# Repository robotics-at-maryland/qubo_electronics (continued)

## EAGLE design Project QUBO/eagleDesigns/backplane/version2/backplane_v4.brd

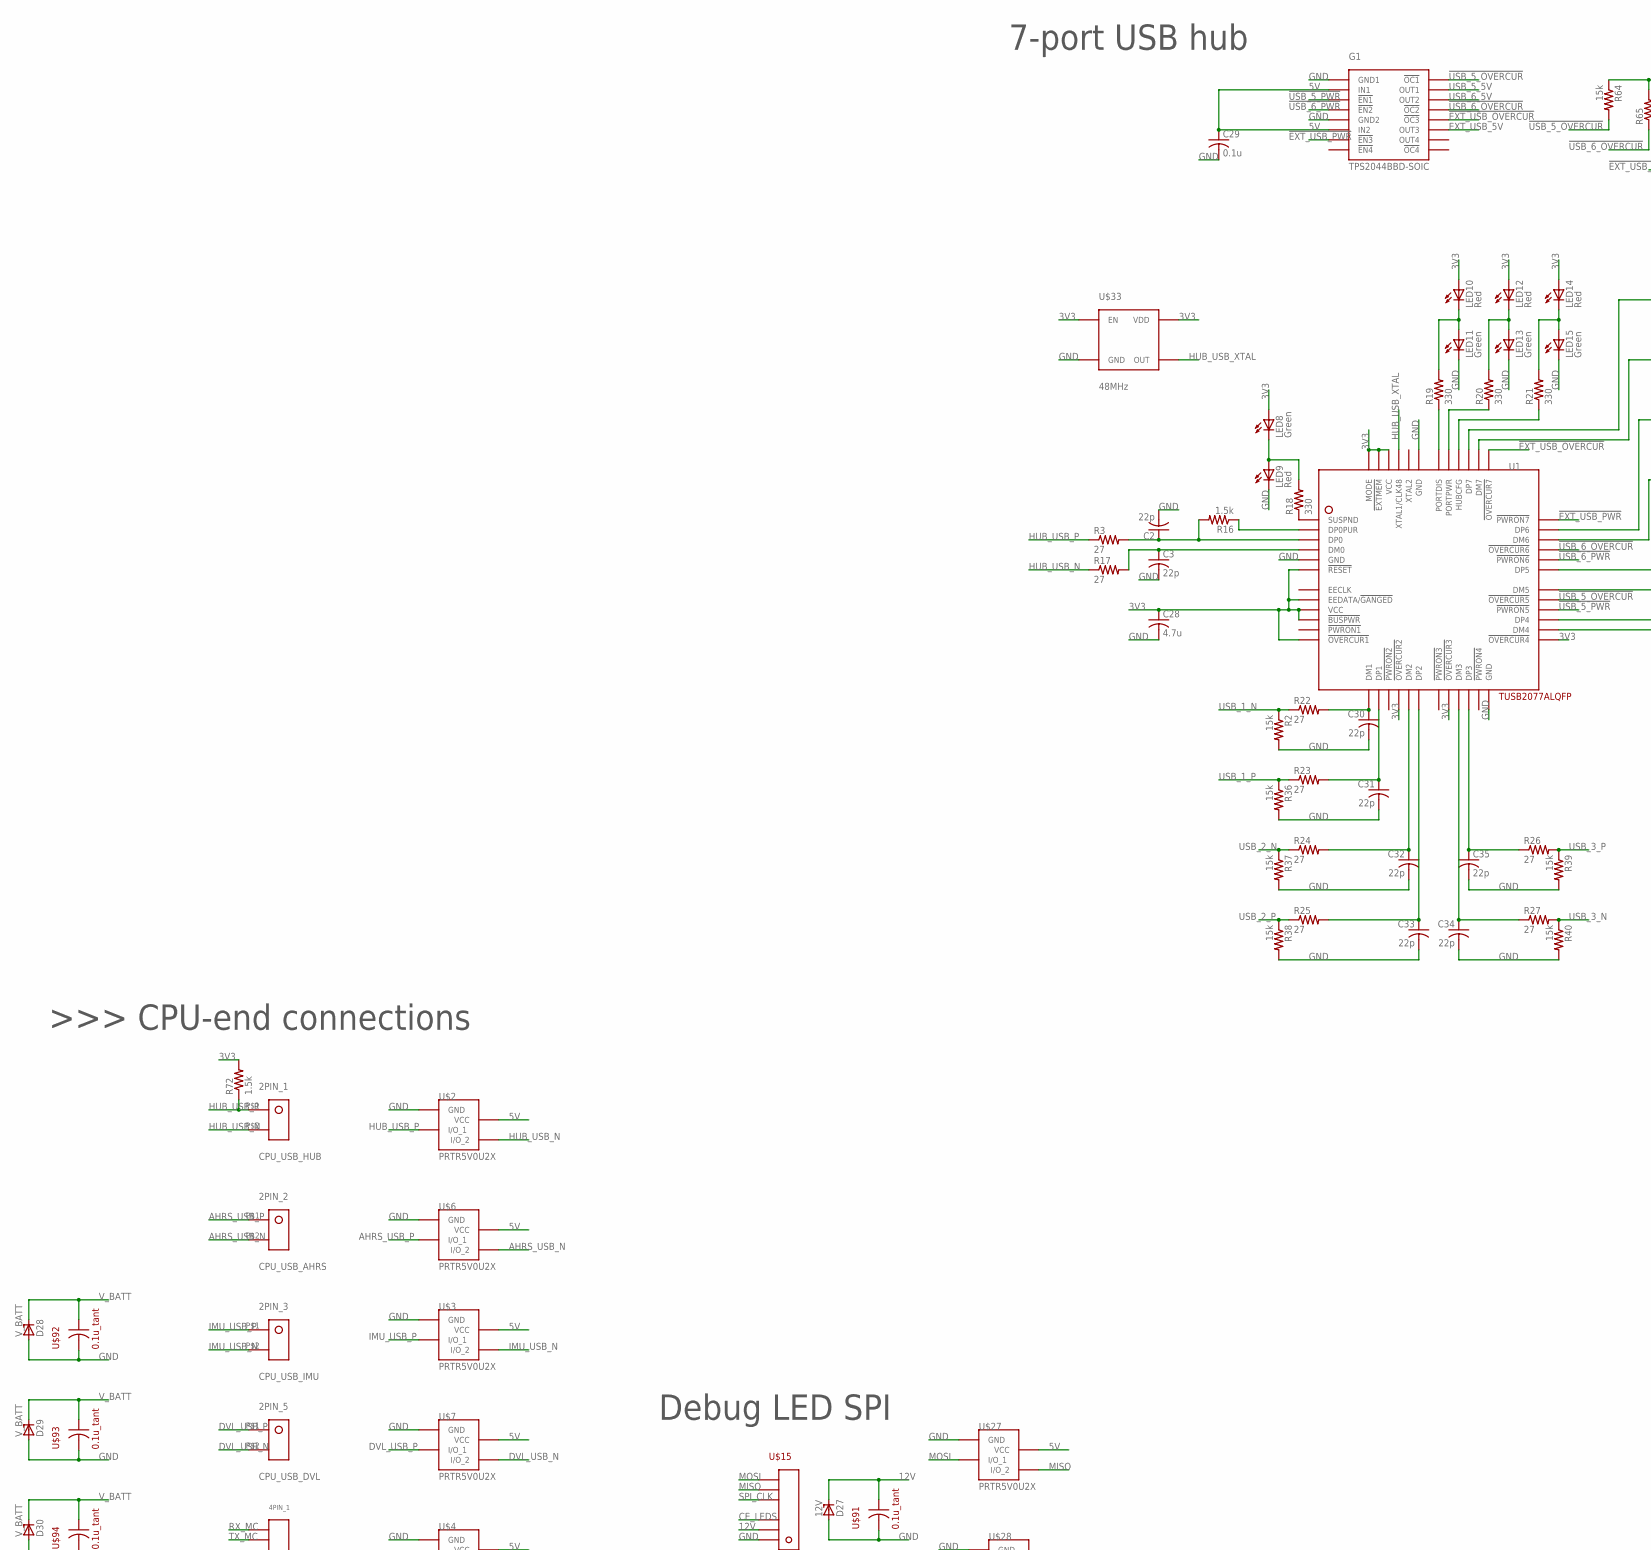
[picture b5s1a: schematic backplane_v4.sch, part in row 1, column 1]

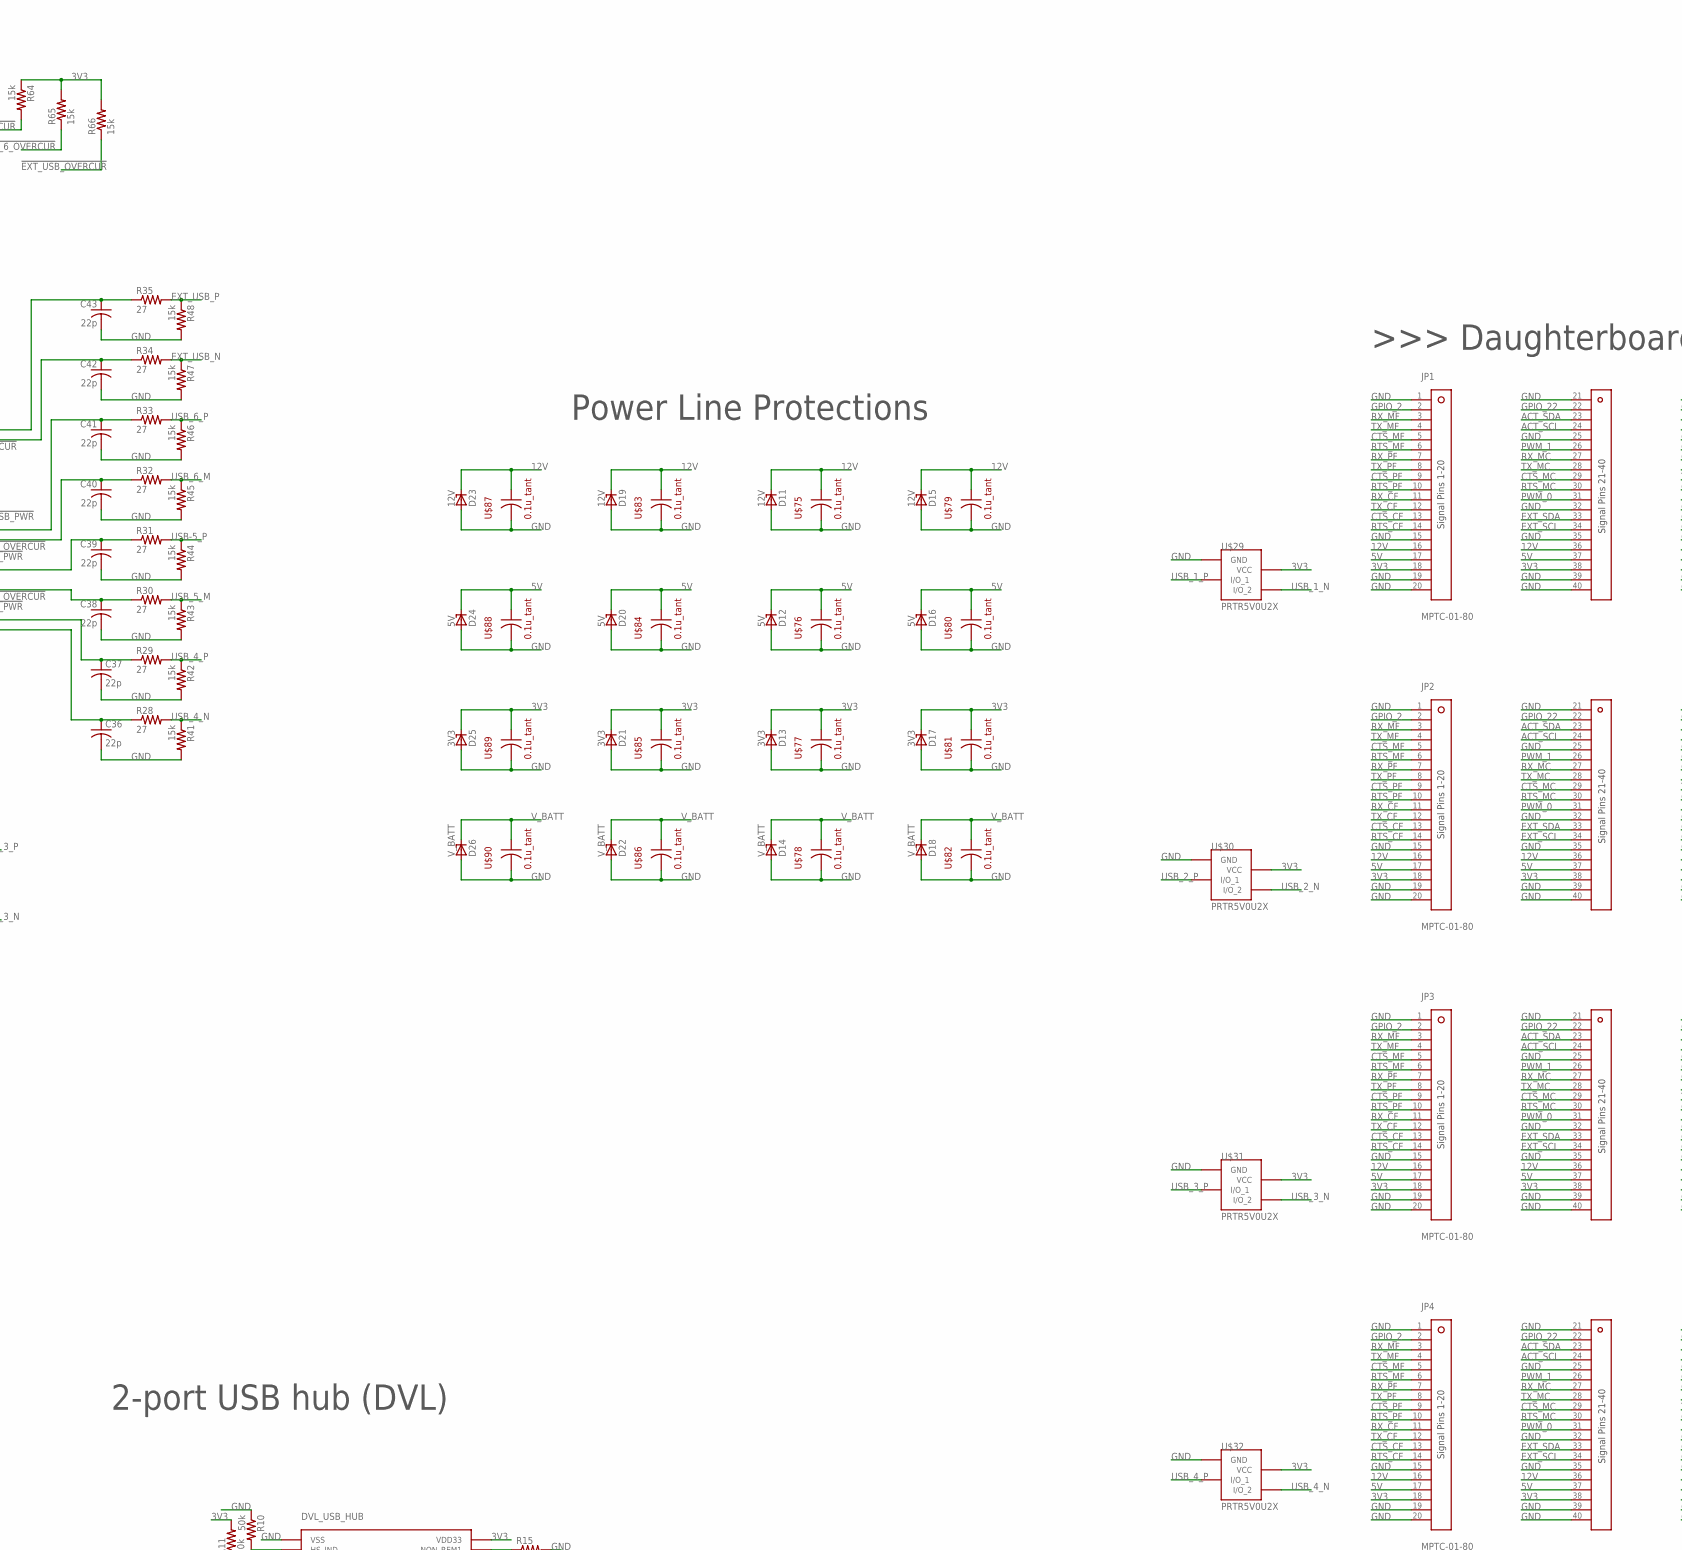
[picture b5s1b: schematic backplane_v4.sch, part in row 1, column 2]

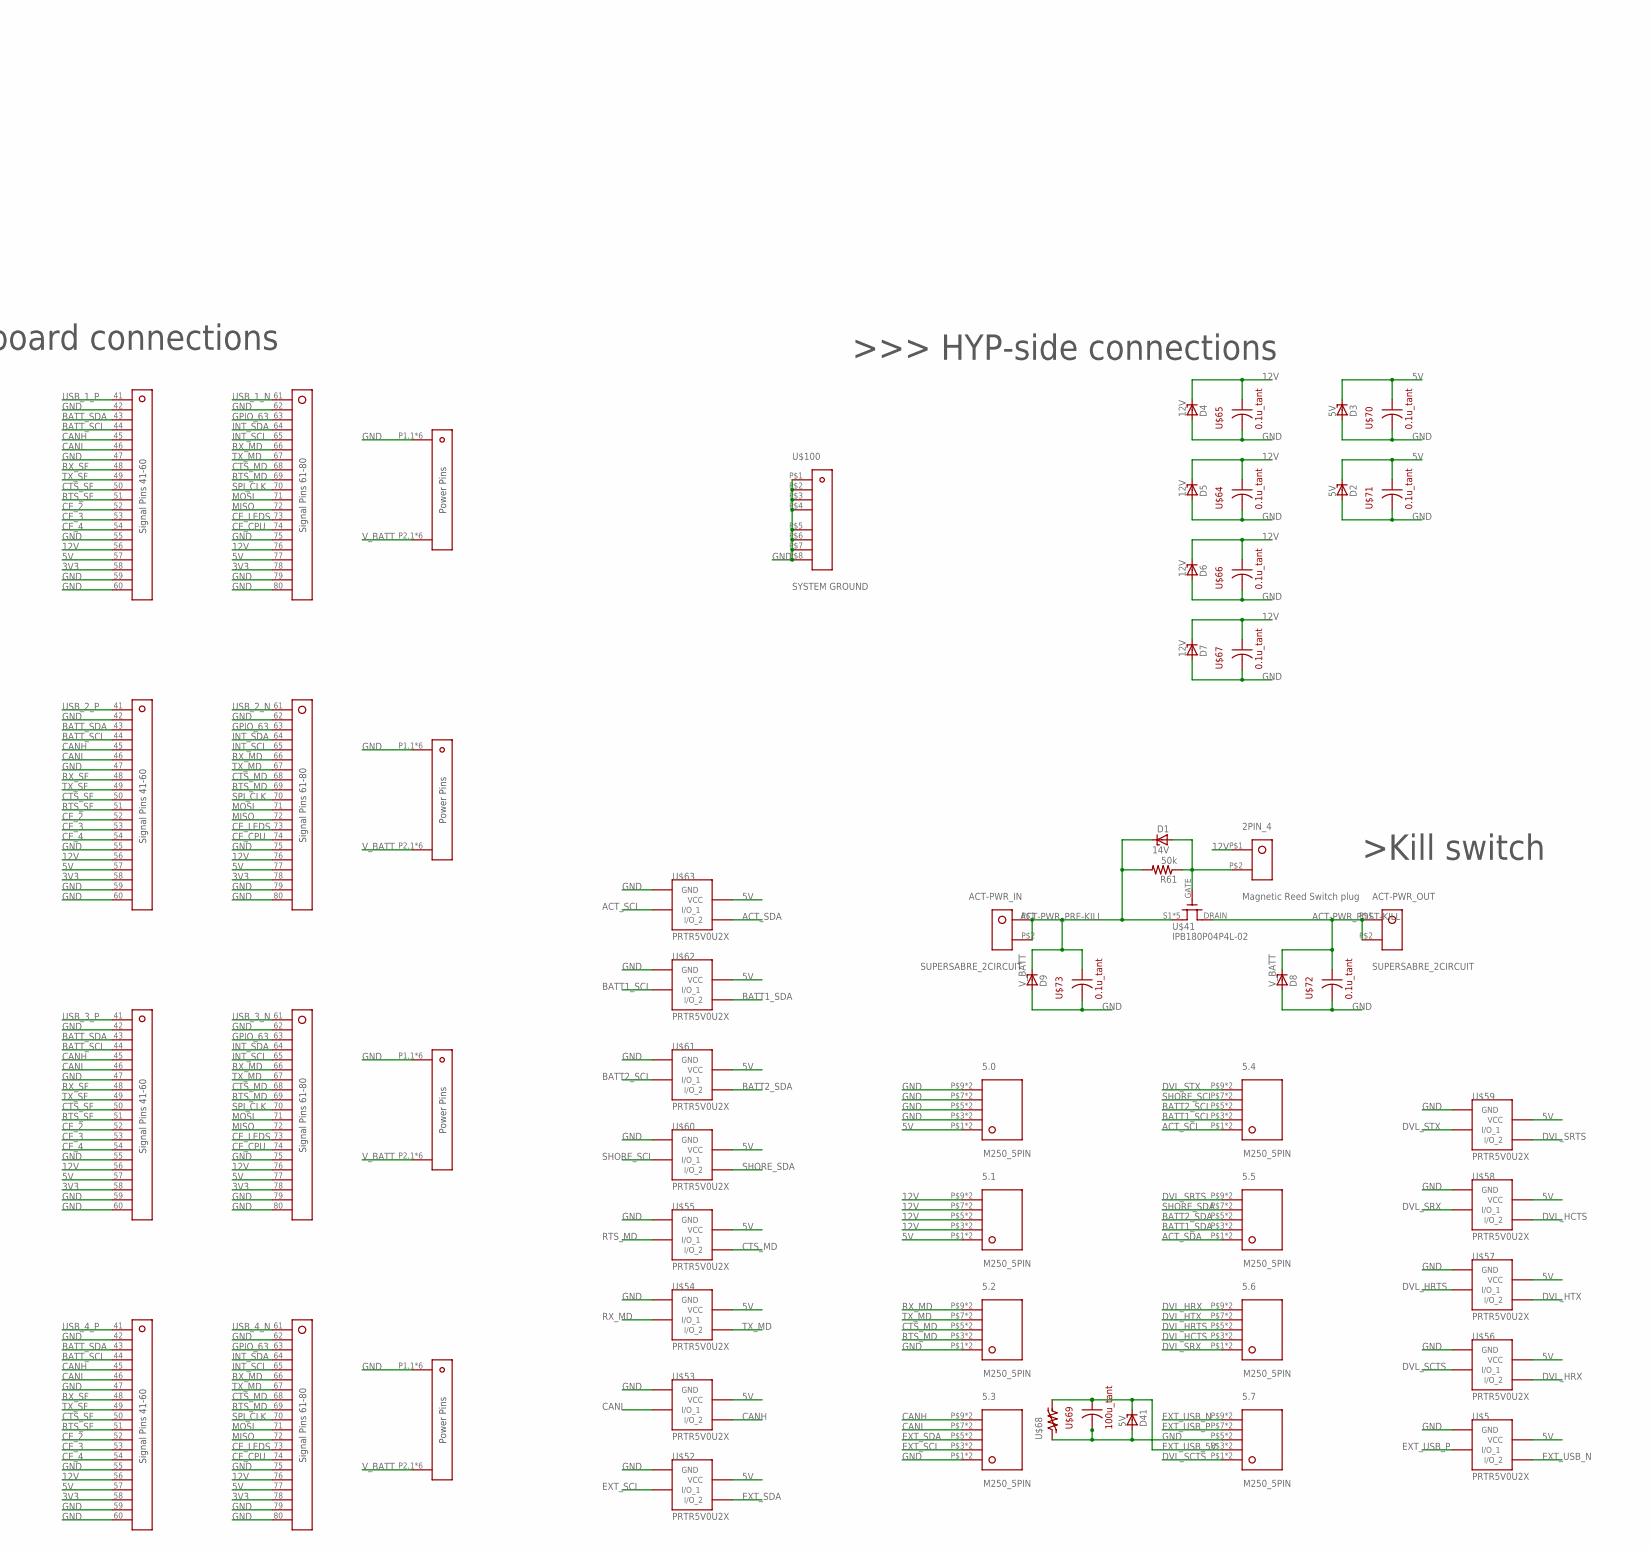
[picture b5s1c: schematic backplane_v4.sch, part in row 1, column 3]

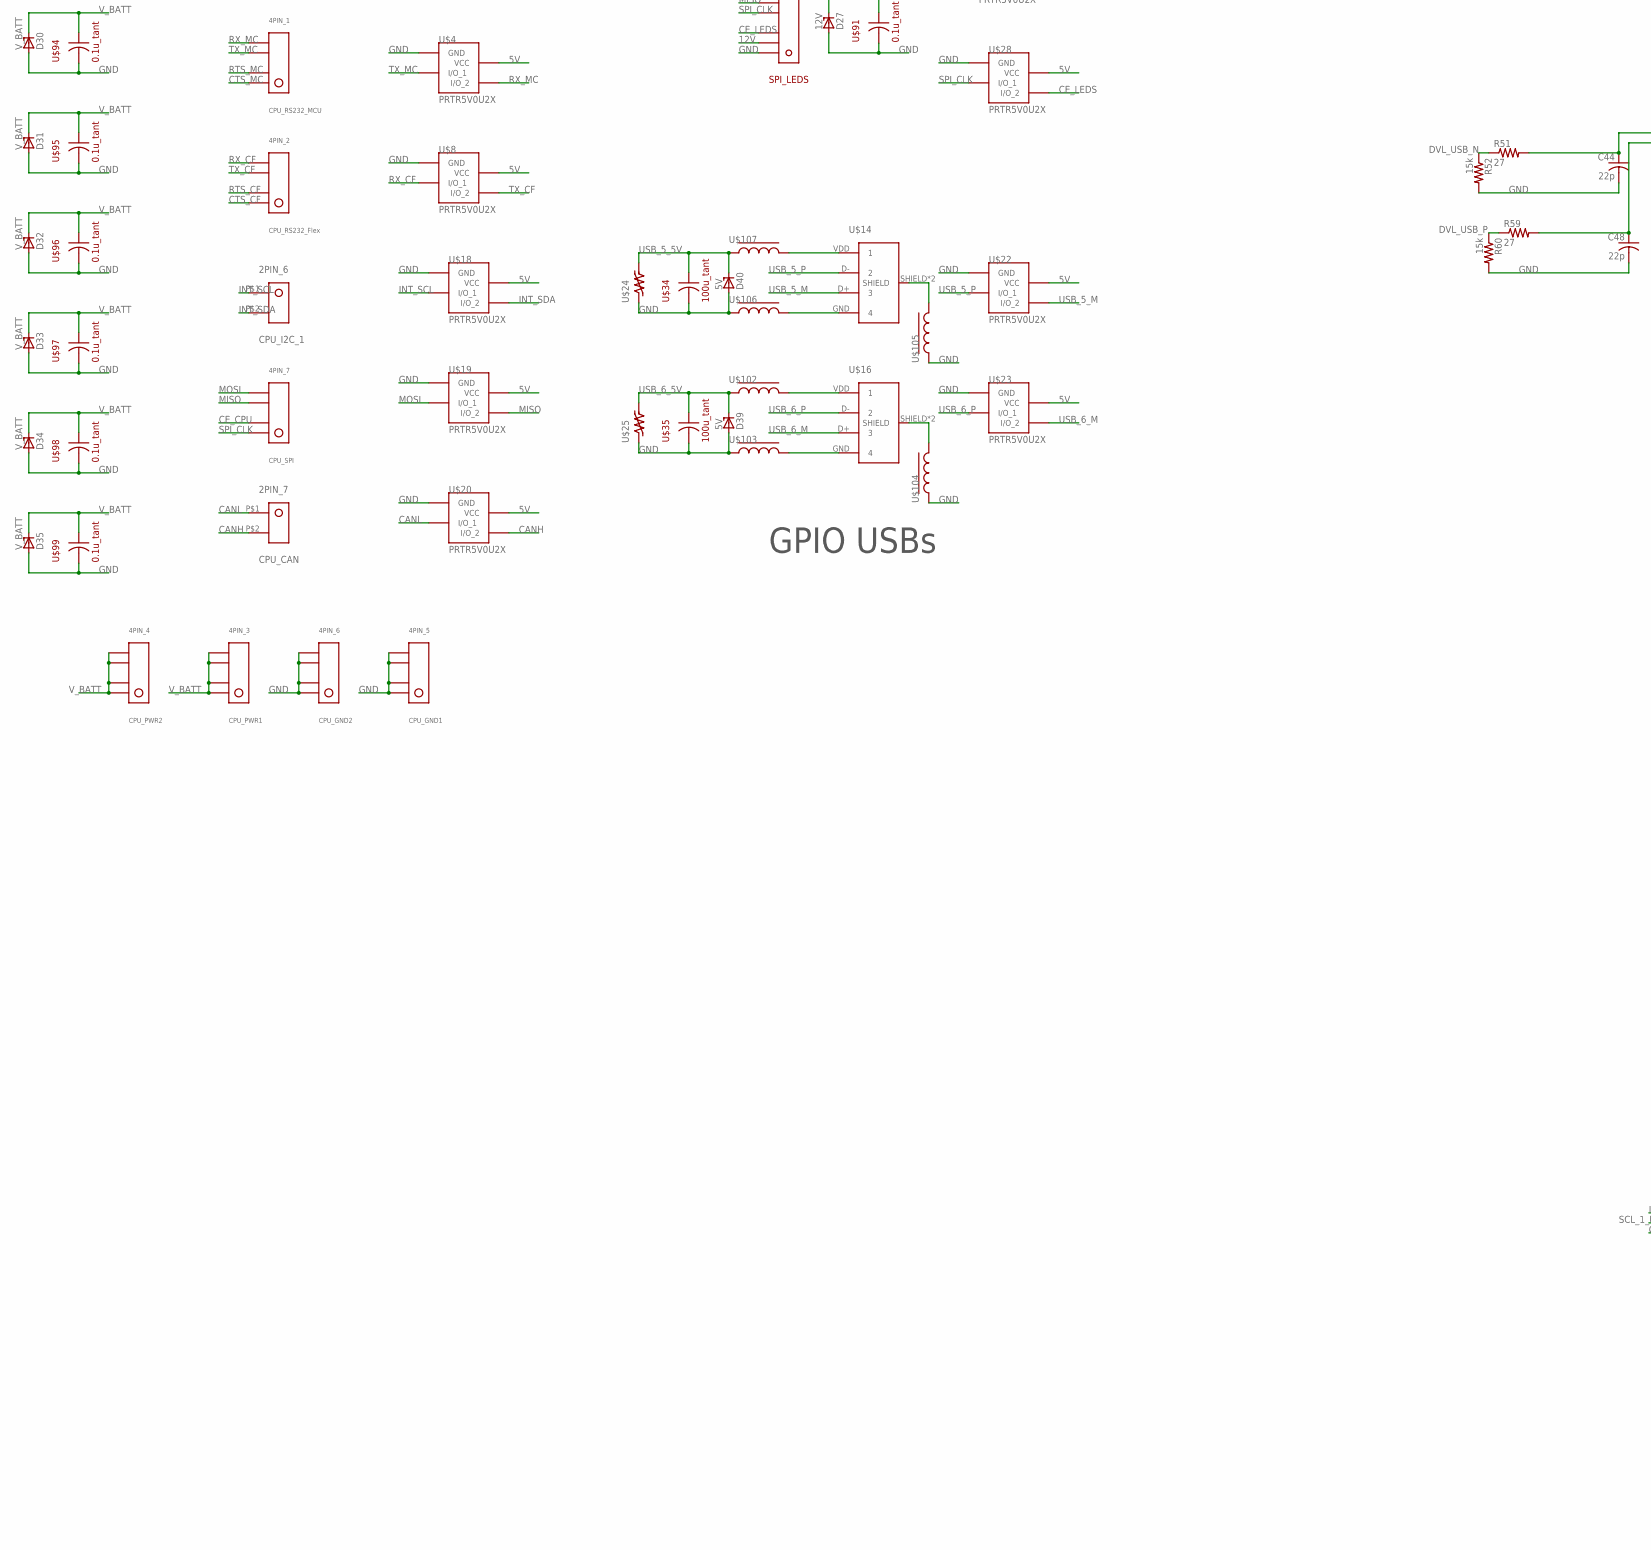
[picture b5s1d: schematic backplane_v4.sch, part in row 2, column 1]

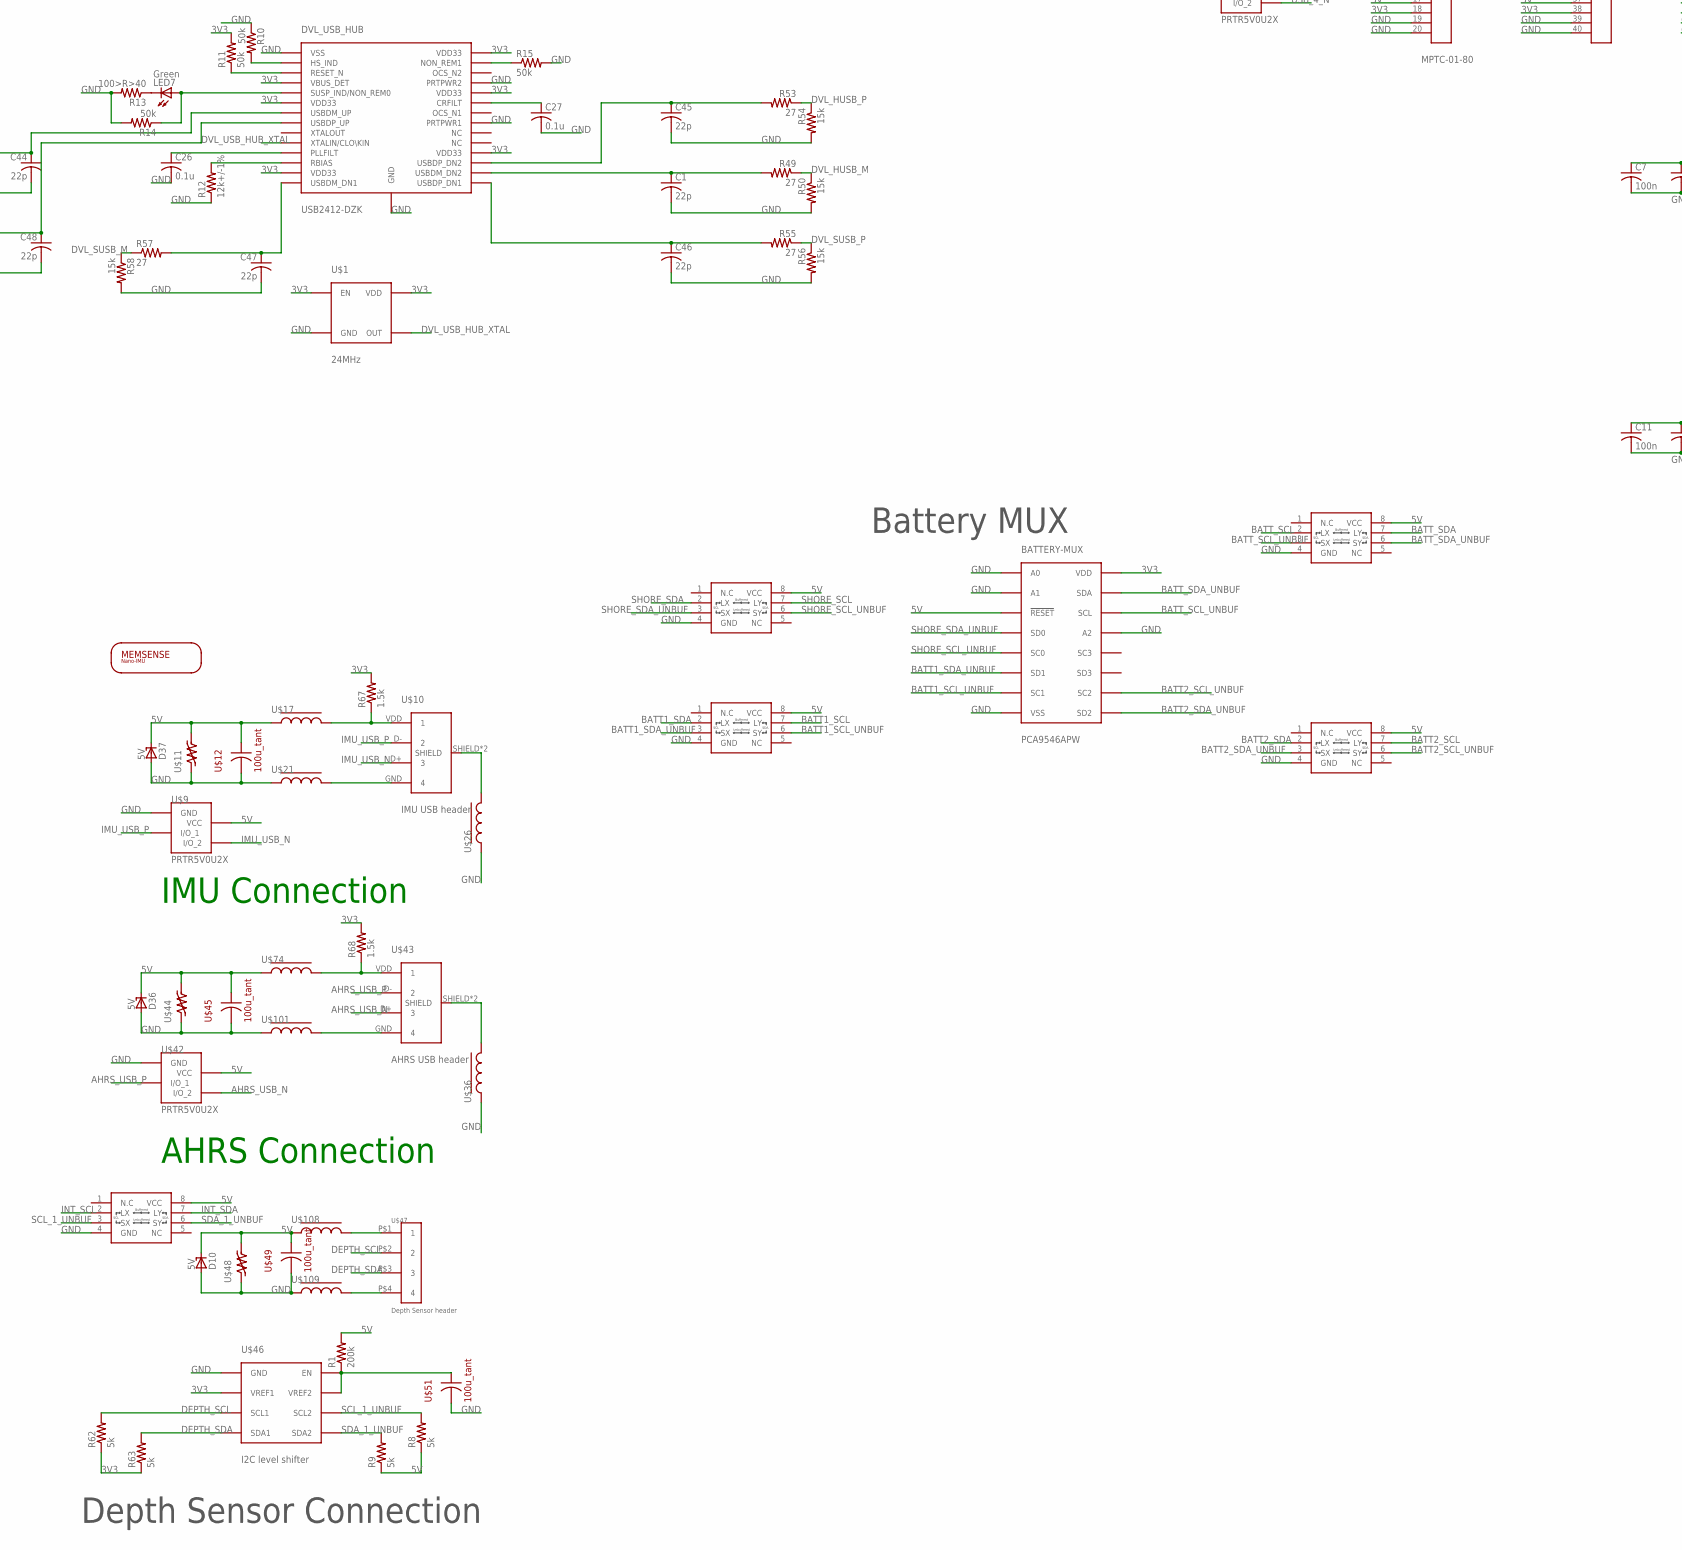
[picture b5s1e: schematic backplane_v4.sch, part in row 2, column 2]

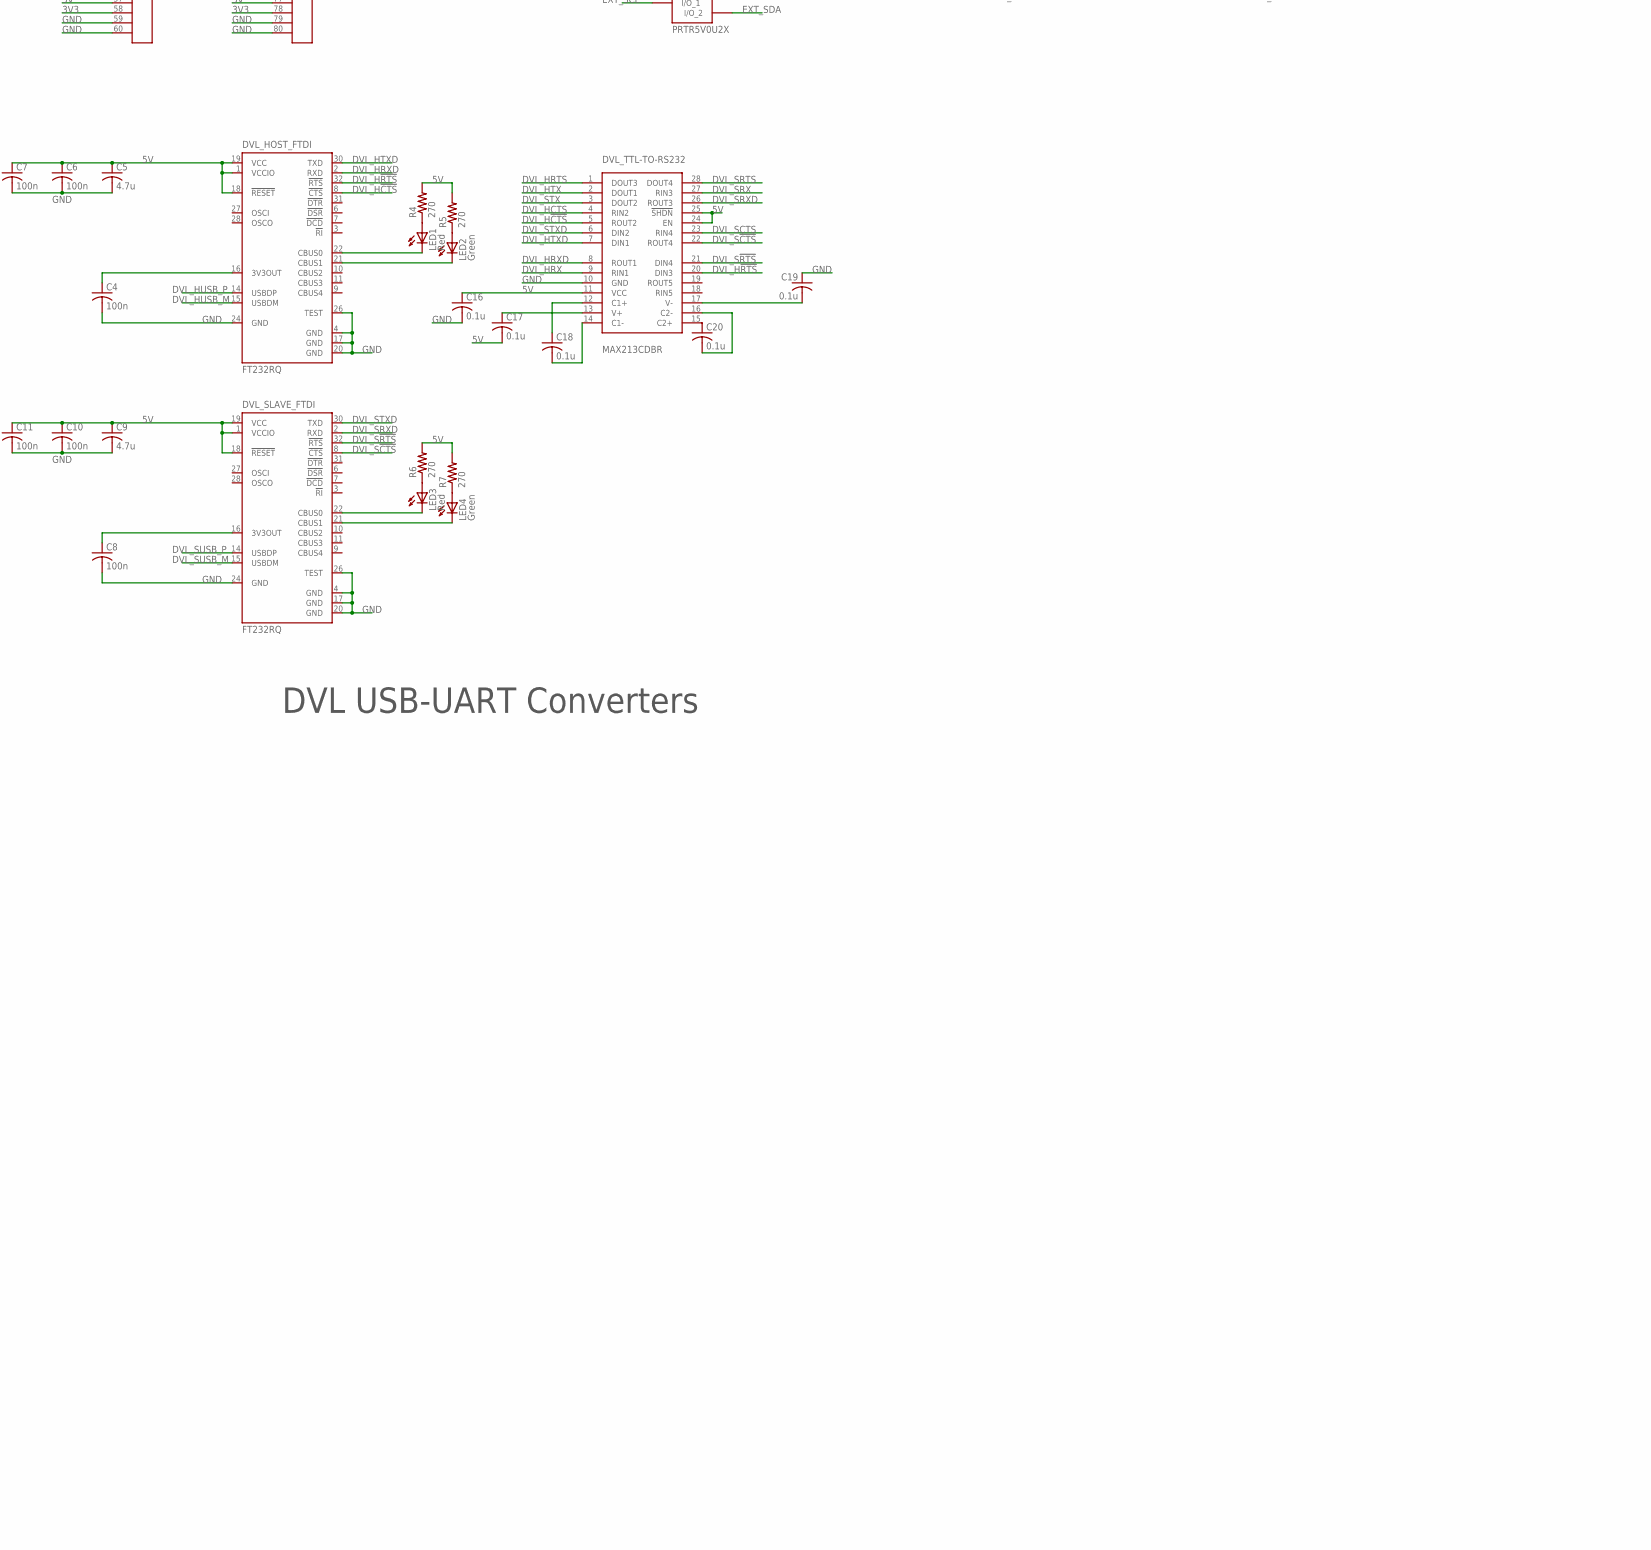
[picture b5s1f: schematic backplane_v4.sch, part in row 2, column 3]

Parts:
2PIN_1: CPU_USB_HUB; KK254_VERT_2PIN
2PIN_2: CPU_USB_AHRS; KK254_VERT_2PIN
2PIN_3: CPU_USB_IMU; KK254_VERT_2PIN
2PIN_4: Magnetic Reed Switch plug; KK254_VERT_2PIN
2PIN_5: CPU_USB_DVL; KK254_VERT_2PIN
2PIN_6: CPU_I2C_1; KK254_VERT_2PIN
2PIN_7: CPU_CAN; KK254_VERT_2PIN
4PIN_1: CPU_RS232_MCU; KK254_VERT_4PIN
4PIN_2: CPU_RS232_Flex; KK254_VERT_4PIN
4PIN_3: CPU_PWR1; KK254_VERT_4PIN
4PIN_4: CPU_PWR2; KK254_VERT_4PIN
4PIN_5: CPU_GND1; KK254_VERT_4PIN
4PIN_6: CPU_GND2; KK254_VERT_4PIN
4PIN_7: CPU_SPI; KK254_VERT_4PIN
5.0, 5.1, 5.2, 5.3, 5.4, 5.5, 5.6, 5.7: M250_5PIN; M205_5PIN
ACT-PWR_IN: SUPERSABRE_2CIRCUIT
ACT-PWR_OUT: SUPERSABRE_2CIRCUIT
BATTERY-MUX: PCA9546APW; TSSOP16
C1, C2, C3, C30, C31, C32, C33, C34, C35, C36, C37, C38, C39, C40, C41, C42, C43, C44, C45, C46, C47, C48: 22p; C0805
C4, C6, C7, C8, C10, C11: 100n; C0805
C5, C9, C28: 4.7u; C0805
C16, C17, C18, C19, C20, C26, C27, C29: 0.1u; C0805
D1: 14V; SOD123
D2, D3, D10, D12, D16, D20, D24, D36, D37, D39, D40, D41: 5V; SOD123
D4, D5, D6, D7, D11, D15, D19, D23, D27: 12V; SOD123
D8, D9, D14, D18, D22, D26, D28, D29, D30, D31, D32, D33, D34, D35: V_BATT; SOD123
D13, D17, D21, D25: 3V3; SOD123
DVL_HOST_FTDI: FT232RQ; QFN32
DVL_SLAVE_FTDI: FT232RQ; QFN32
DVL_TTL-TO-RS232: MAX213CDBR; SSOP28DB
DVL_USB_HUB: USB2412-DZK; QFN-28
G1: TPS2044BBD-SOIC; TPS2044
JP1, JP2, JP3, JP4: MPTC-01-80
LED1, LED3: Red; CHIPLED_0805
LED2, LED4, LED7: Green; CHIPLED_0805
LED8, LED11, LED13, LED15: Green; CHIP-LED0805
LED9, LED10, LED12, LED14: Red; CHIP-LED0805
R1: 200k; R0805
R2, R36, R37, R38, R39, R40, R41, R42, R43, R44, R45, R46, R47, R48, R50, R52, R54, R56, R58, R60, R64, R65, R66: 15k; R0805
R3, R17, R22, R23, R24, R25, R26, R27, R28, R29, R30, R31, R32, R33, R34, R35, R49, R51, R53, R55, R57, R59: 27; R0805
R4, R5, R6, R7: 270; R0805
R8, R9, R62, R63: 5k; R0805
R10, R11, R14, R15, R61: 50k; R0805
R12: 12k+/-1%; R0805
R13: 100>R>40; R0805
R16, R67, R68, R72: 1.5k; R0805
R18, R19, R20, R21: 330; R0805
U1: TUSB2077ALQFP; 48-LQFP_0.5MM_PITCH
U$1: 24MHz; 4-CDFN_3.2X2.5MM
U$2, U$3, U$4, U$5, U$6, U$7, U$8, U$9, U$18, U$19, U$20, U$22, U$23, U$27, U$28, U$29, U$30, U$31, U$32, U$42, U$52, U$53, U$54, U$55, U$56, U$57, U$58, U$59, U$60, U$61, U$62, U$63: PRTR5V0U2X; SOT143B
U$10: IMU USB header; UE27AE54100
U$11, U$24, U$25, U$44, U$48, U$68: V5.5MLA0805; 0805
U$12, U$34, U$35, U$45, U$49, U$51, U$69: 100u_tant; 1206
U$13: MEMSENSE_NIMU
U$14, U$16: USB_4PIN_VERT; UE27AE54100
U$15: SPI_LEDS; KK254_6PIN
U$17, U$21, U$26, U$36, U$74, U$101, U$102, U$103, U$104, U$105, U$106, U$107, U$108, U$109: FERRITE_BEAD; R0805
U$33: 48MHz; 4-CDFN_3.2X2.5MM
U$37, U$38, U$39, U$40, U$50: P82B715; SO8
U$41: IPB180P04P4L-02; PG-TO263-7-3
U$43: AHRS USB header; UE27AE54100
U$46: I2C level shifter; SM8
U$47: Depth Sensor header; DF13-4
U$64, U$65, U$66, U$67, U$70, U$71, U$72, U$73, U$75, U$76, U$77, U$78, U$79, U$80, U$81, U$82, U$83, U$84, U$85, U$86, U$87, U$88, U$89, U$90, U$91, U$92, U$93, U$94, U$95, U$96, U$97, U$98, U$99: 0.1u_tant; 1206
U$100: SYSTEM GROUND; SUPERSABRE_8-PIN

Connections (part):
3V3: BATTERY-MUX.P$16 (VDD), C28.1, D13.C, D17.C, D21.C, D25.C, DVL_USB_HUB.P$4 (VDD33), DVL_USB_HUB.P$10 (VDD33), DVL_USB_HUB.P$14 (VDD33), DVL_USB_HUB.P$18 (VBUS_DET), DVL_USB_HUB.P$20 (VDD33), DVL_USB_HUB.P$27 (VDD33), JP1.18, JP1.38, JP1.58, JP1.78, JP2.18, JP2.38, JP2.58, JP2.78, JP3.18, JP3.38, JP3.58, JP3.78, JP4.18, JP4.38, JP4.58, JP4.78, LED8.A, LED10.A, LED12.A, LED14.A, R11.2, R62.1, R63.1, R64.1, R65.2, R66.2, R67.2, R68.2, R72.2, U1.P$6 (!RESET!), U1.P$8 (EEDATA/!GANGED!), U1.P$9 (VCC), U1.P$10 (!BUSPWR!), U1.P$12 (!OVERCUR1!), U1.P$16 (!OVERCUR2!), U1.P$20 (!OVERCUR3!), U1.P$25 (!OVERCUR4!), U1.P$46 (VCC), U1.P$47 (!EXTMEM!), U1.P$48 (MODE), U$1.P$1 (EN), U$1.P$4 (VDD), U$29.P$4 (VCC), U$30.P$4 (VCC), U$31.P$4 (VCC), U$32.P$4 (VCC), U$33.P$1 (EN), U$33.P$4 (VDD), U$46.P$2 (VREF1), U$77.P$1 (+), U$81.P$1 (+), U$85.P$1 (+), U$89.P$1 (+)
5V: 5.0.P$1, 5.0.P$2, 5.1.P$1, 5.1.P$2, BATTERY-MUX.P$3 (!RESET!), C5.1, C6.1, C7.1, C9.1, C10.1, C11.1, C16.1, C17.2, C29.1, D2.C, D3.C, D10.C, D12.C, D16.C, D20.C, D24.C, D36.C, D37.C, DVL_HOST_FTDI.1 (VCCIO), DVL_HOST_FTDI.18 (!RESET), DVL_HOST_FTDI.19 (VCC), DVL_SLAVE_FTDI.1 (VCCIO), DVL_SLAVE_FTDI.18 (!RESET), DVL_SLAVE_FTDI.19 (VCC), DVL_TTL-TO-RS232.11 (VCC), DVL_TTL-TO-RS232.24 (EN), DVL_TTL-TO-RS232.25 (!SHDN!), G1.IN1, G1.IN2, JP1.17, JP1.37, JP1.57, JP1.77, JP2.17, JP2.37, JP2.57, JP2.77, JP3.17, JP3.37, JP3.57, JP3.77, JP4.17, JP4.37, JP4.57, JP4.77, R1.2, R4.2, R5.2, R6.2, R7.2, R8.1, R9.1, U$2.P$4 (VCC), U$3.P$4 (VCC), U$4.P$4 (VCC), U$5.P$4 (VCC), U$6.P$4 (VCC), U$7.P$4 (VCC), U$8.P$4 (VCC), U$9.P$4 (VCC), U$11.P$2, U$12.P$1 (+), U$17.1, U$18.P$4 (VCC), U$19.P$4 (VCC), U$20.P$4 (VCC), U$22.P$4 (VCC), U$23.P$4 (VCC), U$27.P$4 (VCC), U$28.P$4 (VCC), U$37.8 (VCC), U$38.8 (VCC), U$39.8 (VCC), U$40.8 (VCC), U$42.P$4 (VCC)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
12V: 2PIN_4.P$1, 5.1.P$3, 5.1.P$4, 5.1.P$5, 5.1.P$6, 5.1.P$7, 5.1.P$8, 5.1.P$9, 5.1.P$10, D4.C, D5.C, D6.C, D7.C, D11.C, D15.C, D19.C, D23.C, D27.C, JP1.16, JP1.36, JP1.56, JP1.76, JP2.16, JP2.36, JP2.56, JP2.76, JP3.16, JP3.36, JP3.56, JP3.76, JP4.16, JP4.36, JP4.56, JP4.76, U$15.P$2, U$64.P$1 (+), U$65.P$1 (+), U$66.P$1 (+), U$67.P$1 (+), U$75.P$1 (+), U$79.P$1 (+), U$83.P$1 (+), U$87.P$1 (+), U$91.P$1 (+)
!EXT_USB_OVERCUR!: G1.!OC3!, R66.1, U1.P$37 (!OVERCUR7!)
!EXT_USB_PWR!: G1.!EN3!, U1.P$36 (!PWRON7!)
!USB_5_OVERCUR!: G1.!OC1!, R64.2, U1.P$29 (!OVERCUR5!)
!USB_5_PWR!: G1.!EN1!, U1.P$28 (!PWRON5!)
!USB_6_OVERCUR!: G1.!OC2!, R65.1, U1.P$33 (!OVERCUR6!)
!USB_6_PWR!: G1.!EN2!, U1.P$32 (!PWRON6!)
ACT-PWR_POST-KILL: ACT-PWR_OUT.P$1, ACT-PWR_OUT.P$2, D8.C, U$41.DRAIN, U$72.P$1 (+)
ACT-PWR_PRE-KILL: ACT-PWR_IN.P$1, ACT-PWR_IN.P$2, D1.C, D9.C, R61.2, U$41.S1, U$41.S2, U$41.S3, U$41.S4, U$41.S5, U$73.P$1 (+)
ACT_SCL: 5.4.P$1, 5.4.P$2, JP1.24, JP2.24, JP3.24, JP4.24, U$63.P$2 (I/O_1)
ACT_SDA: 5.5.P$1, 5.5.P$2, JP1.23, JP2.23, JP3.23, JP4.23, U$63.P$3 (I/O_2)
AHRS_USB_N: 2PIN_2.P$2, U$6.P$3 (I/O_2), U$42.P$3 (I/O_2), U$43.D+ (3)
AHRS_USB_P: 2PIN_2.P$1, U$6.P$2 (I/O_1), U$42.P$2 (I/O_1), U$43.D- (2)
BATT1_SCL: 5.4.P$3, 5.4.P$4, U$39.7 (LY), U$62.P$2 (I/O_1)
BATT1_SCL_UNBUF: BATTERY-MUX.P$7 (SC1), U$39.6 (SY)
BATT1_SDA: 5.5.P$3, 5.5.P$4, U$39.2 (LX), U$62.P$3 (I/O_2)
BATT1_SDA_UNBUF: BATTERY-MUX.P$6 (SD1), U$39.3 (SX)
BATT2_SCL: 5.4.P$5, 5.4.P$6, U$37.7 (LY), U$61.P$2 (I/O_1)
BATT2_SCL_UNBUF: BATTERY-MUX.P$10 (SC2), U$37.6 (SY)
BATT2_SDA: 5.5.P$5, 5.5.P$6, U$37.2 (LX), U$61.P$3 (I/O_2)
BATT2_SDA_UNBUF: BATTERY-MUX.P$9 (SD2), U$37.3 (SX)
BATT_SCL: JP1.44, JP2.44, JP3.44, JP4.44, U$38.2 (LX)
BATT_SCL_UNBUF: BATTERY-MUX.P$14 (SCL), U$38.3 (SX)
BATT_SDA: JP1.43, JP2.43, JP3.43, JP4.43, U$38.7 (LY)
BATT_SDA_UNBUF: BATTERY-MUX.P$15 (SDA), U$38.6 (SY)
CANH: 2PIN_7.P$2, 5.3.P$9, 5.3.P$10, JP1.45, JP2.45, JP3.45, JP4.45, U$20.P$3 (I/O_2), U$53.P$3 (I/O_2)
CANL: 2PIN_7.P$1, 5.3.P$7, 5.3.P$8, JP1.46, JP2.46, JP3.46, JP4.46, U$20.P$2 (I/O_1), U$53.P$2 (I/O_1)
CE_2: JP1.52, JP2.52, JP3.52, JP4.52
CE_3: JP1.53, JP2.53, JP3.53, JP4.53
CE_4: JP1.54, JP2.54, JP3.54, JP4.54
CE_CPU: 4PIN_7.P$2, JP1.74, JP2.74, JP3.74, JP4.74
CE_LEDS: JP1.73, JP2.73, JP3.73, JP4.73, U$15.P$3, U$28.P$3 (I/O_2)
CTS_CF: 4PIN_2.P$1, JP1.13, JP2.13, JP3.13, JP4.13
CTS_MC: 4PIN_1.P$1, JP1.29, JP2.29, JP3.29, JP4.29
CTS_MD: 5.2.P$5, 5.2.P$6, JP1.68, JP2.68, JP3.68, JP4.68, U$55.P$3 (I/O_2)
CTS_MF: JP1.5, JP2.5, JP3.5, JP4.5
CTS_PF: JP1.9, JP2.9, JP3.9, JP4.9
CTS_SF: JP1.50, JP2.50, JP3.50, JP4.50
DEPTH_SCL: R62.2, U$46.P$3 (SCL1), U$47.P$2 (2)
DEPTH_SDA: R63.2, U$46.P$4 (SDA1), U$47.P$3 (3)
DVL_H!CTS!: DVL_HOST_FTDI.8 (!CTS), DVL_TTL-TO-RS232.5 (ROUT2)
DVL_H!RTS!: DVL_HOST_FTDI.32 (!RTS), DVL_TTL-TO-RS232.20 (DIN3)
DVL_HCTS: 5.6.P$3, 5.6.P$4, DVL_TTL-TO-RS232.4 (RIN2), U$58.P$3 (I/O_2)
DVL_HRTS: 5.6.P$5, 5.6.P$6, DVL_TTL-TO-RS232.1 (DOUT3), U$57.P$2 (I/O_1)
DVL_HRX: 5.6.P$9, 5.6.P$10, DVL_TTL-TO-RS232.9 (RIN1), U$56.P$3 (I/O_2)
DVL_HRXD: DVL_HOST_FTDI.2 (RXD), DVL_TTL-TO-RS232.8 (ROUT1)
DVL_HTX: 5.6.P$7, 5.6.P$8, DVL_TTL-TO-RS232.2 (DOUT1), U$57.P$3 (I/O_2)
DVL_HTXD: DVL_HOST_FTDI.30 (TXD), DVL_TTL-TO-RS232.7 (DIN1)
DVL_HUSB_M: DVL_HOST_FTDI.15 (USBDM), R49.1, R50.1
DVL_HUSB_P: DVL_HOST_FTDI.14 (USBDP), R53.1, R54.1
DVL_S!CTS!: DVL_SLAVE_FTDI.8 (!CTS), DVL_TTL-TO-RS232.22 (ROUT4)
DVL_S!RTS!: DVL_SLAVE_FTDI.32 (!RTS), DVL_TTL-TO-RS232.21 (DIN4)
DVL_SCTS: 5.7.P$1, 5.7.P$2, DVL_TTL-TO-RS232.23 (RIN4), U$56.P$2 (I/O_1)
DVL_SRTS: 5.5.P$9, 5.5.P$10, DVL_TTL-TO-RS232.28 (DOUT4), U$59.P$3 (I/O_2)
DVL_SRX: 5.6.P$1, 5.6.P$2, DVL_TTL-TO-RS232.27 (RIN3), U$58.P$2 (I/O_1)
DVL_SRXD: DVL_SLAVE_FTDI.2 (RXD), DVL_TTL-TO-RS232.26 (ROUT3)
DVL_STX: 5.4.P$9, 5.4.P$10, DVL_TTL-TO-RS232.3 (DOUT2), U$59.P$2 (I/O_1)
DVL_STXD: DVL_SLAVE_FTDI.30 (TXD), DVL_TTL-TO-RS232.6 (DIN2)
DVL_SUSB_M: DVL_SLAVE_FTDI.15 (USBDM), R57.1, R58.1
DVL_SUSB_P: DVL_SLAVE_FTDI.14 (USBDP), R55.1, R56.1
DVL_USB_HUB_XTAL: DVL_USB_HUB.P$24 (XTALIN/CLO\KIN), U$1.P$3 (OUT)
DVL_USB_N: 2PIN_5.P$2, R51.1, R52.1, U$7.P$3 (I/O_2)
DVL_USB_P: 2PIN_5.P$1, R59.1, R60.1, U$7.P$2 (I/O_1)
EXT_SCL: 5.3.P$3, 5.3.P$4, JP1.34, JP2.34, JP3.34, JP4.34, U$52.P$2 (I/O_1)
EXT_SDA: 5.3.P$5, 5.3.P$6, JP1.33, JP2.33, JP3.33, JP4.33, U$52.P$3 (I/O_2)
EXT_USB_5V: 5.7.P$3, 5.7.P$4, D41.C, G1.OUT3, U$68.P$2, U$69.P$1 (+)
EXT_USB_N: 5.7.P$9, 5.7.P$10, R34.2, R47.1, U$5.P$3 (I/O_2)
EXT_USB_P: 5.7.P$7, 5.7.P$8, R35.2, R48.1, U$5.P$2 (I/O_1)
GND: 4PIN_5.P$1, 4PIN_5.P$2, 4PIN_5.P$3, 4PIN_5.P$4, 4PIN_6.P$1, 4PIN_6.P$2, 4PIN_6.P$3, 4PIN_6.P$4, 5.0.P$3, 5.0.P$4, 5.0.P$5, 5.0.P$6, 5.0.P$7, 5.0.P$8, 5.0.P$9, 5.0.P$10, 5.2.P$1, 5.2.P$2, 5.3.P$1, 5.3.P$2, 5.7.P$5, 5.7.P$6, BATTERY-MUX.P$1 (A0), BATTERY-MUX.P$2 (A1), BATTERY-MUX.P$8 (VSS), BATTERY-MUX.P$13 (A2), C1.2, C2.2, C3.2, C4.2, C5.2, C6.2, C7.2, C8.2, C9.2, C10.2, C11.2, C16.2, C19.1, C26.2, C27.2, C28.2, C29.2, C30.2, C31.2, C32.2, C33.2, C34.2, C35.2, C36.2, C37.2, C38.2, C39.2, C40.2, C41.2, C42.2, C43.2, C44.2, C45.2, C46.2, C47.2, C48.2, D2.A, D3.A, D4.A, D5.A, D6.A, D7.A, D8.A, D9.A, D10.A, D11.A, D12.A, D13.A, D14.A, D15.A, D16.A, D17.A, D18.A, D19.A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
GPIO_2: JP1.2, JP2.2, JP3.2, JP4.2
GPIO_22: JP1.22, JP2.22, JP3.22, JP4.22
GPIO_63: JP1.63, JP2.63, JP3.63, JP4.63
HUB_USB_N: 2PIN_1.P$2, R17.1, U$2.P$3 (I/O_2)
HUB_USB_P: 2PIN_1.P$1, R3.1, R72.1, U$2.P$2 (I/O_1)
HUB_USB_XTAL: U1.P$45 (XTAL1/CLK48), U$33.P$3 (OUT)
IMU_USB_N: 2PIN_3.P$2, U$3.P$3 (I/O_2), U$9.P$3 (I/O_2), U$10.D+ (3)
IMU_USB_P: 2PIN_3.P$1, U$3.P$2 (I/O_1), U$9.P$2 (I/O_1), U$10.D- (2)
INT_SCL: 2PIN_6.P$1, JP1.65, JP2.65, JP3.65, JP4.65, U$18.P$2 (I/O_1), U$50.2 (LX)
INT_SDA: 2PIN_6.P$2, JP1.64, JP2.64, JP3.64, JP4.64, U$18.P$3 (I/O_2), U$50.7 (LY)
KILL-SWT-GATE: 2PIN_4.P$2, D1.A, R61.1, U$41.GATE
MISO: 4PIN_7.P$3, JP1.72, JP2.72, JP3.72, JP4.72, U$15.P$5, U$19.P$3 (I/O_2), U$27.P$3 (I/O_2)
MOSI: 4PIN_7.P$4, JP1.71, JP2.71, JP3.71, JP4.71, U$15.P$6, U$19.P$2 (I/O_1), U$27.P$2 (I/O_1)
unnamed: C8.1, DVL_SLAVE_FTDI.16 (3V3OUT)
unnamed: DVL_SLAVE_FTDI.21 (CBUS1), LED4.C
unnamed: C2.1, R3.2, R16.2, U1.P$3 (DP0)
unnamed: R16.1, U1.P$2 (DP0PUR)
unnamed: R18.1, U1.P$1 (SUSPND)
unnamed: R19.1, U1.P$42 (PORTDIS)
unnamed: C3.1, R17.2, U1.P$4 (DM0)
unnamed: LED8.C, LED9.A, R18.2
unnamed: LED10.C, LED11.A, R19.2
unnamed: LED14.C, LED15.A, R21.2
unnamed: R21.1, U1.P$40 (HUBCFG)
unnamed: LED12.C, LED13.A, R20.2
unnamed: C30.1, R22.2, U1.P$13 (DM1)
unnamed: C31.1, R23.2, U1.P$14 (DP1)
unnamed: C32.1, R24.2, U1.P$17 (DM2)
unnamed: R20.1, U1.P$41 (PORTPWR)
unnamed: C34.1, R27.1, U1.P$21 (DM3)
unnamed: C35.1, R26.1, U1.P$22 (DP3)
unnamed: DVL_SLAVE_FTDI.22 (CBUS0), LED3.C
unnamed: LED3.A, R6.1
unnamed: LED4.A, R7.1
unnamed: C4.1, DVL_HOST_FTDI.16 (3V3OUT)
unnamed: R67.1, U$10.VDD (1), U$17.2
unnamed: U$10.GND (4), U$21.2
unnamed: U$10.SHIELD, U$10.SHIELD1 (SHIELD), U$26.2
unnamed: U$47.P$1 (1), U$108.2
unnamed: C18.1, DVL_TTL-TO-RS232.12 (C1+)
unnamed: C18.2, DVL_TTL-TO-RS232.14 (C1-)
unnamed: DVL_HOST_FTDI.21 (CBUS1), LED2.C
unnamed: DVL_HOST_FTDI.22 (CBUS0), LED1.C
unnamed: C20.2, DVL_TTL-TO-RS232.16 (C2-)
unnamed: LED7.C, R13.1
unnamed: U$47.P$4 (4), U$109.2
unnamed: R68.1, U$43.VDD (1), U$74.2
unnamed: R1.1, U$46.P$7 (VREF2), U$46.P$8 (EN), U$51.P$1 (+)
unnamed: U$43.GND (4), U$101.2
unnamed: U$36.2, U$43.SHIELD, U$43.SHIELD1 (SHIELD)
unnamed: U$14.VDD (1), U$107.2
unnamed: LED1.A, R4.1
unnamed: LED2.A, R5.1
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
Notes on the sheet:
IMU Connection
Debug LED SPI
GPIO USBs
7-port USB hub
2-port USB hub (DVL)
Battery MUX
DVL USB-UART Converters
AHRS Connection
Depth Sensor Connection
Power Line Protections
